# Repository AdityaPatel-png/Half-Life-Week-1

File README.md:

Keyboard But better
My project is a mechanical gaming keyboard combined with a doc and a touchpad. 
Essentially, it has some keys from a standard keyboard (wasd, num keys, ctrl, c & v) that will fulfill most need from an external piece.
It also will connect with a touchpad which will give a better experience if it is used when connected to a smartphone or tablet.
Finally, It will have a MicroSD slot and a USB A and C port (USB A is power only) because external storage is cool and you can never have too too many USBs.
The brain of my PCB is a Raspberry Pi Pico. 

# Bill of Materials (BOM)

| Item | Amount | Cost (ea.) | Link |
| :--- | :---: | :---: | :--- |
| Raspberry Pi Pico | 1 | $4.00 | [Raspberry Pi](https://www.pishop.us/product/raspberry-pi-pico/?src=raspberrypi) |
| MX Switches | 18 | $0.35 | [Divinkey](https://divinikey.com/products/cherry-mx2a-black-linear-switches?_pos=1&_sid=84ffd3377&_ss=r) |
| PCB Fabrication | 1 | $4.00 | [JLCPCB](https://jlcpcb.com) |
| FPC Ribbon Dock | 1 | $0.88 | [Mouser](https://www.mouser.com/en/ProductDetail/Molex/505110-1297?qs=W0yvOO0ixfGYeJVj%2FXWh6w%3D%3D) |
| Cirque GlidePoint | 1 | $12.52 | [Mouser](https://www.mouser.com/en/ProductDetail/Cirque/TM040040-2024-302?qs=wd5RIQLrsJgMzmw571gvDw%3D%3D) |
| **Total (each kit)** | **1** | **$27.7** | |

Already Owned (not listed here): Keycaps, resistors (5kΩ), MicroSD slot, USB A and C receptacls

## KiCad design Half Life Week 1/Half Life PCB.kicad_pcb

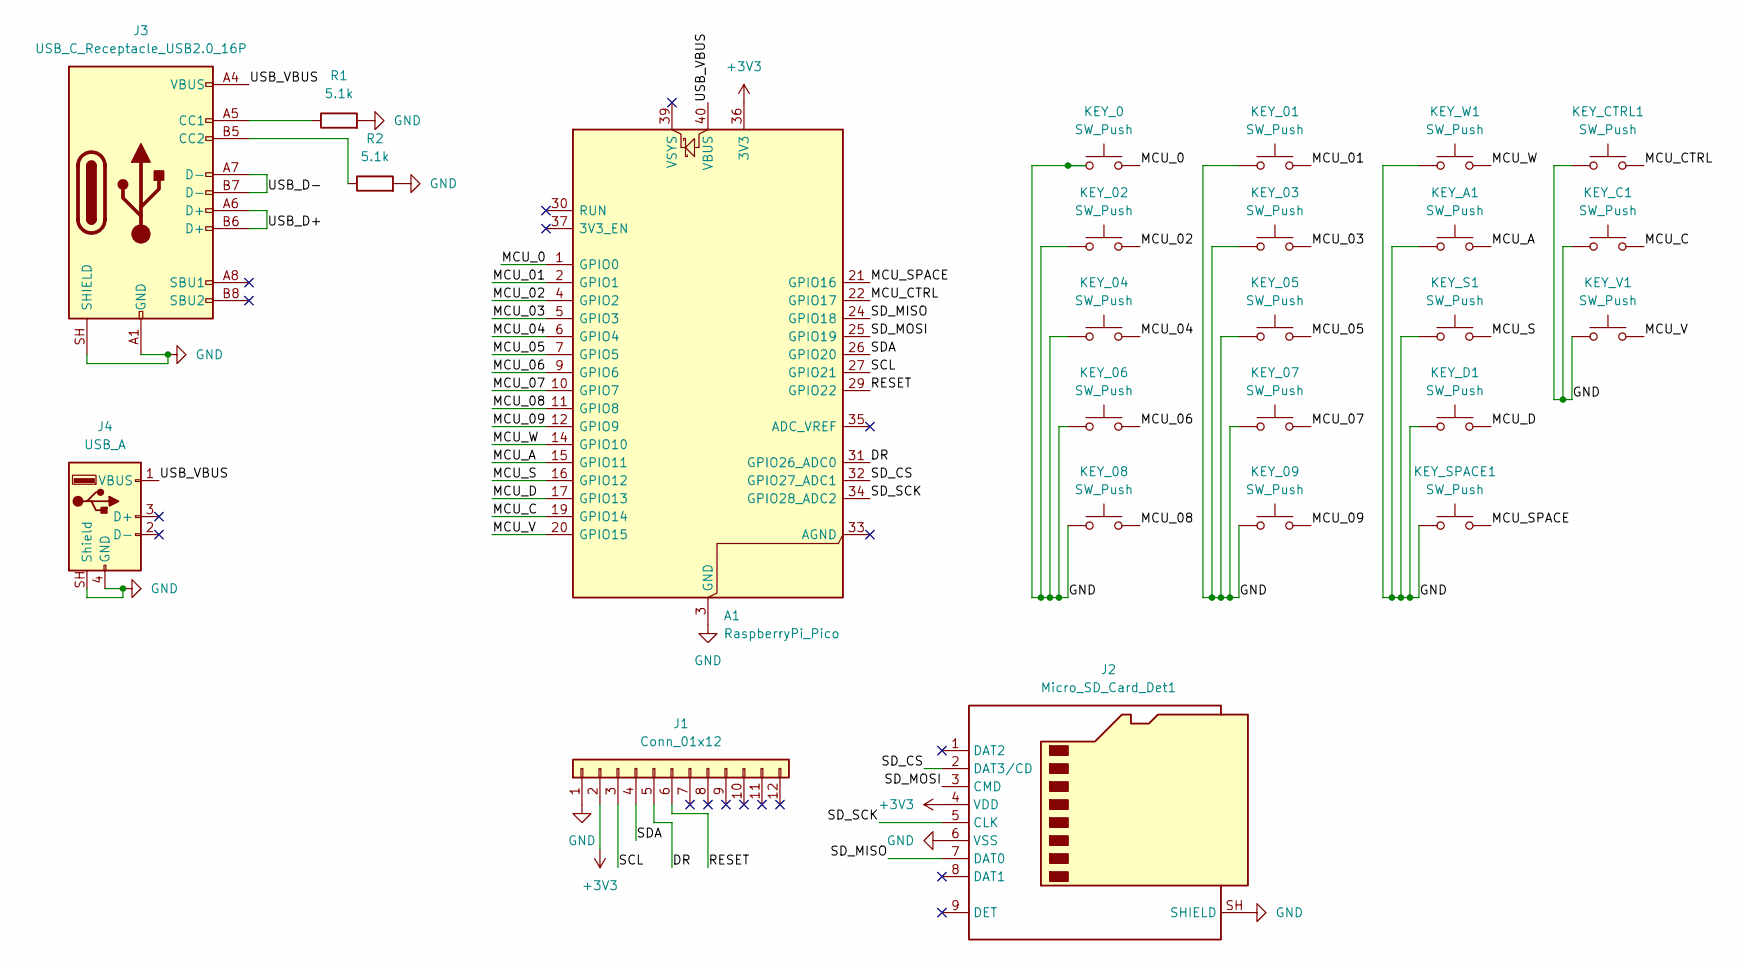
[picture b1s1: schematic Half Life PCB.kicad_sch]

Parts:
A1: RaspberryPi_Pico; RaspberryPi_Pico_Common_Unspecified
J1: Conn_01x12; Hirose_FH12-12S-0.5SH_1x12-1MP_P0.50mm_Horizontal
J2: Micro_SD_Card_Det1; microSD_HC_Wuerth_693072010801
J3: USB_C_Receptacle_USB2.0_16P; USB_C_Receptacle_HRO_TYPE-C-31-M-12
J4: USB_A; USB_A_Wuerth_614004134726_Horizontal
KEY_0, KEY_01, KEY_02, KEY_03, KEY_04, KEY_05, KEY_06, KEY_07, KEY_08, KEY_09: SW_Push; SW_Cherry_MX_1.00u_PCB
KEY_A1: SW_Push; SW_Cherry_MX_1.00u_PCB
KEY_C1: SW_Push; SW_Cherry_MX_1.00u_PCB
KEY_CTRL1: SW_Push; SW_Cherry_MX_1.00u_PCB
KEY_D1: SW_Push; SW_Cherry_MX_1.00u_PCB
KEY_S1: SW_Push; SW_Cherry_MX_1.00u_PCB
KEY_SPACE1: SW_Push; SW_Cherry_MX_6.25u_PCB
KEY_V1: SW_Push; SW_Cherry_MX_1.00u_PCB
KEY_W1: SW_Push; SW_Cherry_MX_1.00u_PCB
R1, R2: 5.1k; R_0805_2012Metric

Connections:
+3V3: A1.36 (3V3), J1.2, J2.4 (VDD)
/DR: A1.31 (GPIO26_ADC0), J1.5
/MCU_0: A1.1 (GPIO0), KEY_0.2
/MCU_01: A1.2 (GPIO1), KEY_01.2
/MCU_02: A1.4 (GPIO2), KEY_02.2
/MCU_03: A1.5 (GPIO3), KEY_03.2
/MCU_04: A1.6 (GPIO4), KEY_04.2
/MCU_05: A1.7 (GPIO5), KEY_05.2
/MCU_06: A1.9 (GPIO6), KEY_06.2
/MCU_07: A1.10 (GPIO7), KEY_07.2
/MCU_08: A1.11 (GPIO8), KEY_08.2
/MCU_09: A1.12 (GPIO9), KEY_09.2
/MCU_A: A1.15 (GPIO11), KEY_A1.2
/MCU_C: A1.19 (GPIO14), KEY_C1.2
/MCU_CTRL: A1.22 (GPIO17), KEY_CTRL1.2
/MCU_D: A1.17 (GPIO13), KEY_D1.2
/MCU_S: A1.16 (GPIO12), KEY_S1.2
/MCU_SPACE: A1.21 (GPIO16), KEY_SPACE1.2
/MCU_V: A1.20 (GPIO15), KEY_V1.2
/MCU_W: A1.14 (GPIO10), KEY_W1.2
/RESET: A1.29 (GPIO22), J1.6
/SCL: A1.27 (GPIO21), J1.3
/SDA: A1.26 (GPIO20), J1.4
/SD_CS: A1.32 (GPIO27_ADC1), J2.2 (DAT3/CD)
/SD_MISO: A1.24 (GPIO18), J2.7 (DAT0)
/SD_MOSI: A1.25 (GPIO19), J2.3 (CMD)
/SD_SCK: A1.34 (GPIO28_ADC2), J2.5 (CLK)
/USB_D+: J3.A6 (D+), J3.B6 (D+)
/USB_D-: J3.A7 (D-), J3.B7 (D-)
/USB_VBUS: A1.40 (VBUS), J3.A4 (VBUS), J3.A9 (VBUS), J3.B4 (VBUS), J3.B9 (VBUS), J4.1 (VBUS)
GND: A1.3 (GND), A1.8 (GND), A1.13 (GND), A1.18 (GND), A1.23 (GND), A1.28 (GND), A1.38 (GND), J1.1, J2.6 (VSS), J2.SH (SHIELD), J3.A1 (GND), J3.A12 (GND), J3.B1 (GND), J3.B12 (GND), J3.SH (SHIELD), J4.4 (GND), J4.SH (Shield), KEY_0.1, KEY_01.1, KEY_02.1, KEY_03.1, KEY_04.1, KEY_05.1, KEY_06.1, KEY_07.1, KEY_08.1, KEY_09.1, KEY_A1.1, KEY_C1.1, KEY_CTRL1.1, KEY_D1.1, KEY_S1.1, KEY_SPACE1.1, KEY_V1.1, KEY_W1.1, R1.2, R2.2
unnamed: J3.A5 (CC1), R1.1
unnamed: J3.B5 (CC2), R2.1

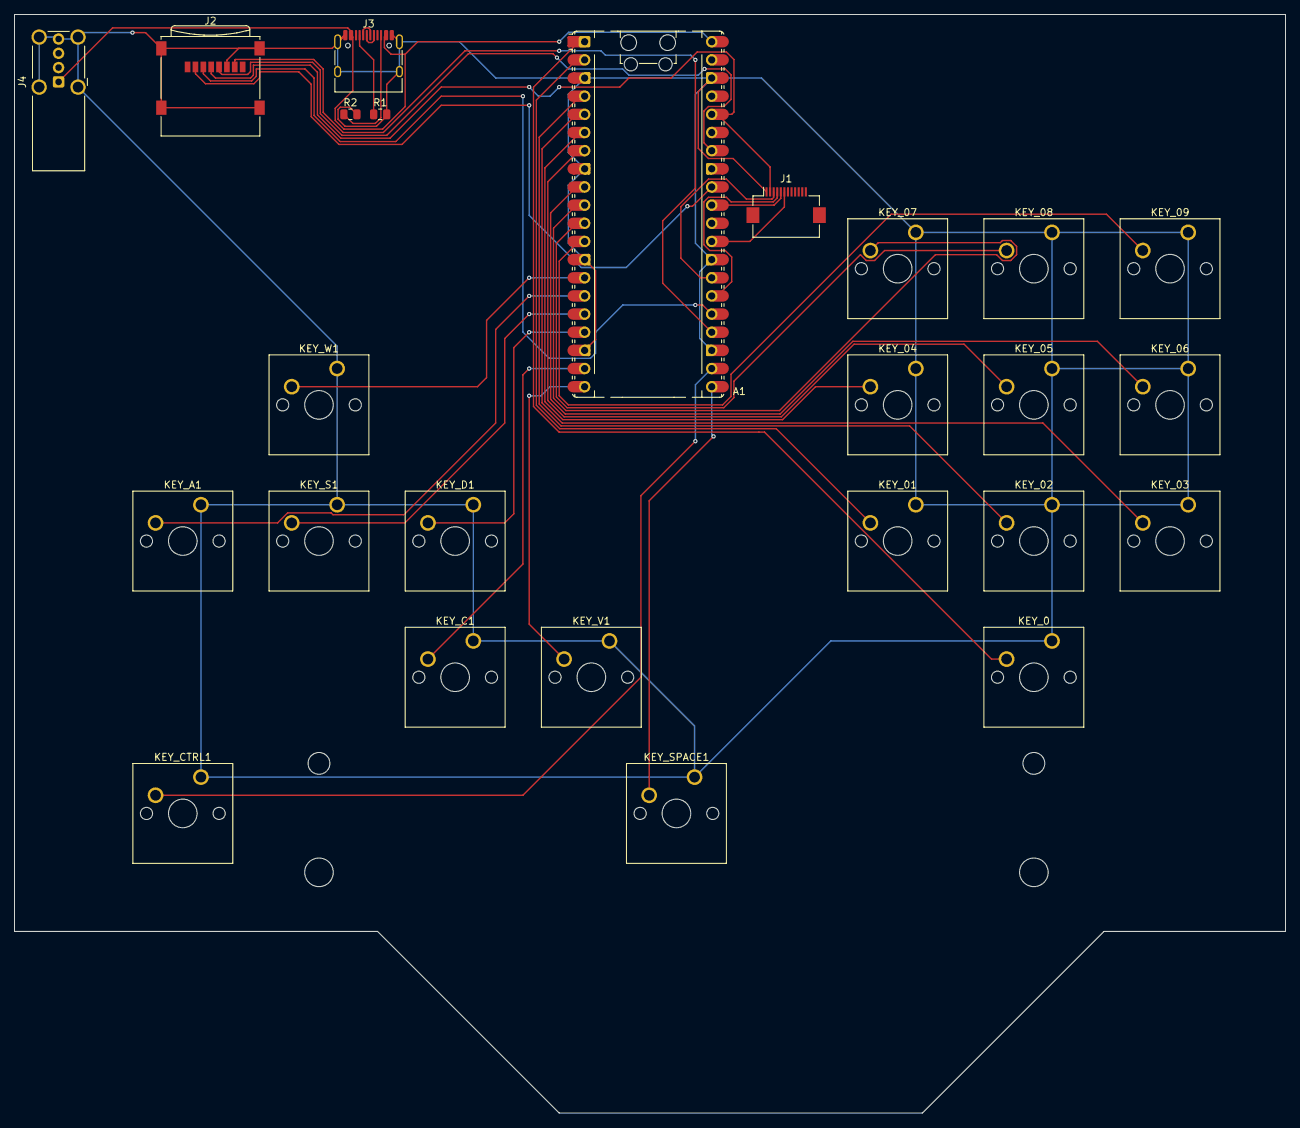
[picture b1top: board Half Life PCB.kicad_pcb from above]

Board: 2 copper layers, 177.8 x 153.7 mm, 25 parts (0 on the bottom side), 33 nets.

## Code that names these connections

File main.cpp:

// Note to self: The pico is not registering on device as of writing the code, so make sure it does before running hardware. (Maybe switch it to arduino so its easier if thats possible somehow)

#include <stdio.h>
#include <pico/stdlib.h>
#include <hardware/gpio.h>
#include <hardware/i2c.h>

#define I2C_PORT i2c1
const u_int32_t PIN_SDA = 26;
const u_int32_t PIN_SCL = 27;
const u_int32_t PIN_DR = 31;
const u_int32_t PIN_RST = 29;
const u_int32_t PIN_SD_CS = 32;
const u_int32_t PIN_SD_SCK = 24;
const u_int32_t PIN_SD_MOSI = 25;
const u_int32_t PIN_SD_MISO = 34;

const u_int32_t NUM_KEYS = 18;
const u_int32_t KEY_PINS[NUM_KEYS] = {
    10, 11, 12, 13, 14, 15,
    0, 1, 2, 3, 4, 5, 6, 7, 
    8, 9, 16, 17
};

void init_gpio_input(uintptr_t gpio_pin) {
    gpio_init(gpio_pin);
    gpio_pin_dir(gpio_pin, GPIO_IN);
    gpio_pin_pull_up(gpio_pin);
};

void init_touchpad_i2c() {
    i2c_init(TOUCHPAD_I2C_PORT, 400*1000 );
    gpio_set_function(PIN_SDA, GPIO_FUNC_I2C);
    gpio_set_function(PIN_SCL, GPIO_FUNC_I2C);
    gpio_pull_up(PIN_SDA);
    gpio_pull_up(PIN_SCL);
    gpio_init(PIN_DR);
    gpio_set_dir(PIN_DR, GPIO_IN);
    gpio_init(PIN_RST);
    gpio_set_dir(PIN_RST, GPIO_OUT);
    gpio_put(PIN_RESET, 0);
    sleep_ms(20);
    gpio_put(PIN_RESET, 1);
}

int main() {
    studio_init_all();
    sleep_ms(2000);

    for (u_int32_t i = 0; i < NUM_KEYS; i++) {
        init_gpio_input(KEY_PINS[i]);
    }

    init_touchpad_i2c();
    
    while (true)
    {
        for (uintptr_t i = 0; i < NUM_KEYS; i++) {
            if (!gpio_get(KEY_PINS[i])) 
            {
                printf("SWITCH ON KEY %d\n ACTIVE /n", KEY_PINS[i]);
            }
        }

        if (gpio_get(PIN_DR)) {
            uintptr_t buffer[6];

            int bytes_read = i2c_read_blocking(TOUCHPAD_I2C_PORT, 0x2A, buffer, 6, false);

            if (bytes_read>0) {
                u_int16_t x = (buffer[2] & 0x0F) << 8| buffer[1];
                u_int16_t y = (buffer[4] & 0x0F) << 8| buffer[3];
            }
        }

        sleep_ms(8);
    }
    
    return 0;
}
